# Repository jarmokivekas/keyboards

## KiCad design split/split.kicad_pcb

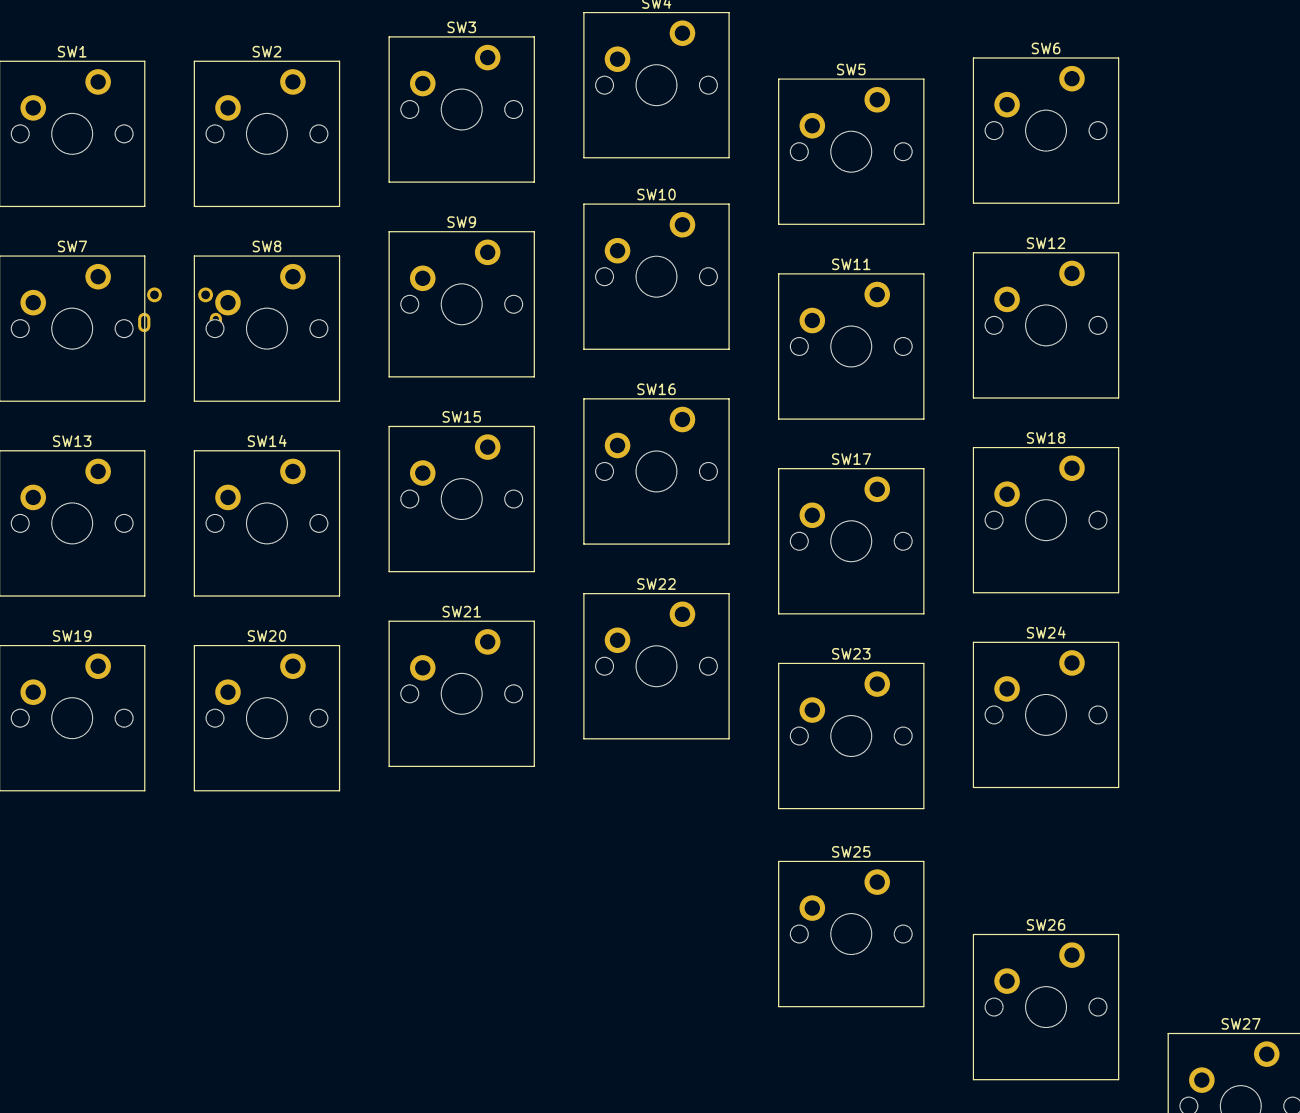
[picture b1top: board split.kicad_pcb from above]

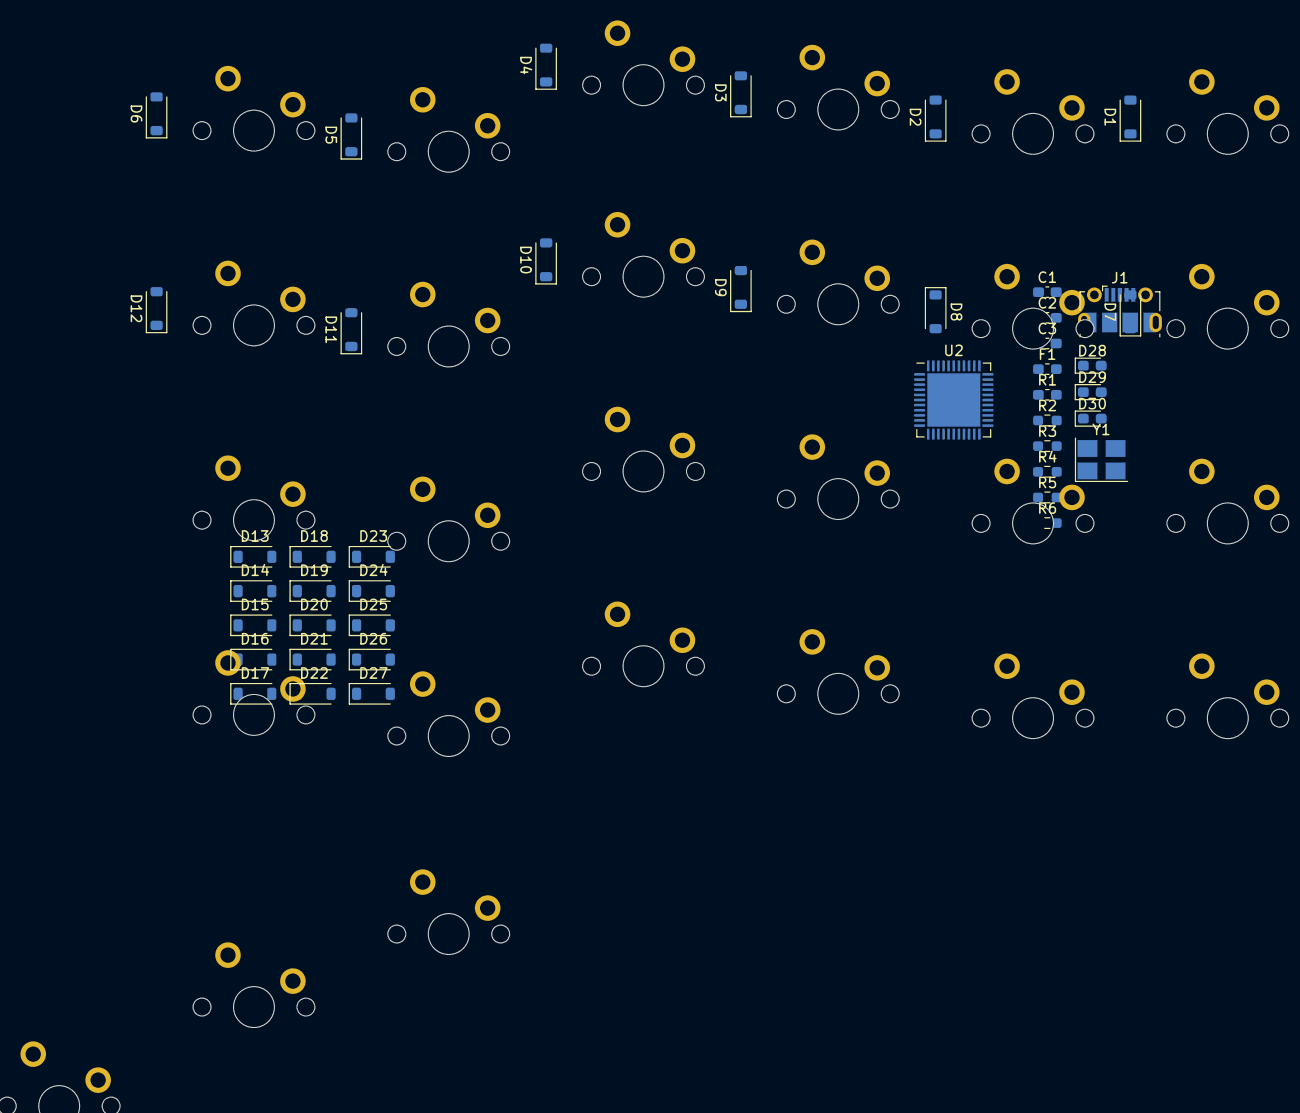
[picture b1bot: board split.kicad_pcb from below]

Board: 2 copper layers, 70 parts (43 on the bottom side), 54 nets, no tracks yet.

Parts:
C1, C2: 22pF; C_0603_1608Metric_Pad1.08x0.95mm_HandSolder
C3: 1uF; C_0603_1608Metric_Pad1.08x0.95mm_HandSolder
D1, D2, D3, D4, D5, D6, D7, D8, D9, D10, D11, D12, D13, D14, D15, D16, D17, D18, D19, D20, D21, D22, D23, D24, D25, D26, D27: 1N4148W; D_SOD-123
D28, D29, D30: LED; LED_0603_1608Metric_Pad1.05x0.95mm_HandSolder
F1: 500mA; Fuse_0603_1608Metric_Pad1.05x0.95mm_HandSolder
J1: USB_B_Micro; USB_Micro-B_Molex-105017-0001
R1: 1K; Fuse_0603_1608Metric_Pad1.05x0.95mm_HandSolder
R2, R6: 1K; R_0603_1608Metric_Pad0.98x0.95mm_HandSolder
R3, R4: 22R; R_0603_1608Metric_Pad0.98x0.95mm_HandSolder
R5: 10K; R_0603_1608Metric_Pad0.98x0.95mm_HandSolder
SW1, SW2, SW3, SW4, SW5, SW6, SW7, SW8, SW9, SW10, SW11, SW12, SW13, SW14, SW15, SW16, SW17, SW18, SW19, SW20, SW21, SW22, SW23, SW24, SW25, SW26, SW27: SW_Push_45deg; MX_PCB_1.00u
U2: ATmega32U4-M; QFN-44-1EP_7x7mm_P0.5mm_EP5.2x5.2mm
Y1: 16MHz; Oscillator_SMD_Abracon_ASE-4Pin_3.2x2.5mm_HandSoldering

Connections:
/controller/D+: R4.2, U2.4 (D+)
/controller/D-: R3.2, U2.3 (D-)
/controller/UVCC: F1.1, J1.1 (VBUS), U2.2 (UVCC), U2.7 (VBUS)
/key-matrix/COL0: SW1.1, SW7.1, SW13.1, SW19.1
/key-matrix/COL1: SW2.1, SW8.1, SW14.1, SW20.1
/key-matrix/COL2: SW3.1, SW9.1, SW15.1, SW21.1
/key-matrix/COL3: SW4.1, SW10.1, SW16.1, SW22.1, SW25.1
/key-matrix/COL4: SW5.1, SW11.1, SW17.1, SW23.1, SW26.1
/key-matrix/COL5: SW6.1, SW12.1, SW18.1, SW24.1, SW27.1
/key-matrix/ROW0: D1.1 (K), D2.1 (K), D3.1 (K), D4.1 (K), D5.1 (K), D6.1 (K)
/key-matrix/ROW1: D7.1 (K), D8.1 (K), D9.1 (K), D10.1 (K), D11.1 (K), D12.1 (K)
/key-matrix/ROW2: D13.1 (K), D14.1 (K), D15.1 (K), D16.1 (K), D17.1 (K), D18.1 (K)
/key-matrix/ROW3: D19.1 (K), D20.1 (K), D21.1 (K), D22.1 (K), D23.1 (K), D24.1 (K)
/key-matrix/ROW4: D25.1 (K), D26.1 (K), D27.1 (K)
GND: C1.1, C2.1, C3.1, J1.5 (GND), J1.6 (Shield), R6.1, U2.5 (UGND), U2.15 (GND), U2.23 (GND), U2.35 (GND), U2.43 (GND), U2.45 (GND), Y1.2, Y1.4
unnamed: D1.2 (A), SW1.2
unnamed: D2.2 (A), SW2.2
unnamed: D3.2 (A), SW3.2
unnamed: D4.2 (A), SW4.2
unnamed: D5.2 (A), SW5.2
unnamed: D6.2 (A), SW6.2
unnamed: D7.2 (A), SW7.2
unnamed: D8.2 (A), SW8.2
unnamed: D9.2 (A), SW9.2
unnamed: D10.2 (A), SW10.2
unnamed: D11.2 (A), SW11.2
unnamed: D12.2 (A), SW12.2
unnamed: D13.2 (A), SW13.2
unnamed: D14.2 (A), SW14.2
unnamed: D15.2 (A), SW15.2
unnamed: D16.2 (A), SW16.2
unnamed: D17.2 (A), SW17.2
unnamed: D18.2 (A), SW18.2
unnamed: D19.2 (A), SW19.2
unnamed: D20.2 (A), SW20.2
unnamed: D21.2 (A), SW21.2
unnamed: D22.2 (A), SW22.2
unnamed: D23.2 (A), SW23.2
unnamed: D24.2 (A), SW24.2
unnamed: D25.2 (A), SW25.2
unnamed: D26.2 (A), SW26.2
unnamed: D27.2 (A), SW27.2
unnamed: D28.1 (K), R2.1
unnamed: D29.1 (K), R1.1
unnamed: D30.1 (K), R6.2
unnamed: J1.3 (D+), R4.1
unnamed: J1.2 (D-), R3.1
unnamed: R2.2, U2.8 (PB0)
unnamed: R1.2, U2.22 (PD5)
unnamed: C3.2, U2.6 (UCAP)
unnamed: C1.2, U2.17 (XTAL1), Y1.1
unnamed: C2.2, U2.16 (XTAL2), Y1.3
unnamed: R5.2, U2.13 (~RESET)
VCC: D28.2 (A), D29.2 (A), D30.2 (A), F1.2, R5.1, U2.14 (VCC), U2.24 (AVCC), U2.34 (VCC), U2.44 (AVCC)

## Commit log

2024-02-07 init split
2024-02-07 start split rigth layout
2024-02-08 add arduino pro micro equivalent MCU schematic
2024-02-08 track scotto kicad library files
